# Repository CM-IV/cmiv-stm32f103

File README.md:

## Introduction

[*Project Link*](https://github.com/CM-IV/cmiv-stm32f103-rs)

A few months ago, my embedded systems experience was limited to collecting temperature and accelerometer data on an ESP32-C3 dev board using Rust. Coming from a computer science background, I had written plenty of C++ code and JavaScript in my first jobs out of college, but aside from school studies I didn't know much about the hardware side of things. I noticed the ESP32-C3-DevKit-RUST-1 dev board and decided try it out, but working with pre-built development boards only showed me half the picture.

I wanted to understand the *why* behind the hardware: Why does I²C require pull-up resistors? Why does my carefully written Rust code fail when the PCB layout is flawed? To answer these questions, I embarked on designing my own 2-layer STM32F103 breakout board in KiCAD 9 (on GNU/Linux, of course). The board includes pinouts for SWD, UART, I²C, and GPIO. This journey was a crash course in humility, teaching me that schematic optimism is no match for LCSC’s inventory constraints. Footprint reviews and BOM checks aren’t just best practices—they’re the difference between a functional PCB and hours of frustration with a soldering iron.

## Design

### Why STM32F103?

I chose the STM32F103 microcontroller for its affordability and versatility. It’s part of the ARM Cortex-M3 series, offering a solid balance of performance and peripherals. With its rich feature set, including SPI, I²C, UART, and GPIO it was perfect for my project.

### Power Delivery

The first step in the design process was laying out the power delivery section of the schematic. Proper power delivery is critical for stable operation. I included 100nF and 10µF decoupling capacitors (C1–C8)—one pair for each VDD pin on the IC. These capacitors help filter noise and stabilize the power supply. Additionally, I added a 120Ω ferrite bead (FB1) to filter power on the analog side, ensuring clean power delivery to sensitive components.

Placement is key. In the PCB layout, these capacitors and the ferrite bead are positioned as close as possible to the microcontroller. This minimizes inductance and ensures reliable power delivery, allowing the microcontroller to boot up as expected.

### Reset Circuit (NRST)

The NRST pin is connected to ground through a 100nF capacitor for electromagnetic shielding and to prevent parasitic reset issues. STM32 microcontrollers have an internal pull-up resistor on the NRST pin, so it can be left floating. For my use case, I'm relying on the SWD pinout for flashing and debugging, making the NRST pin less critical. However, I labeled the NRST net in the schematic for easy identification during PCB design.

### Boot Mode Configuration (BOOT0)

The BOOT0 pin is connected to a 10kΩ series resistor and a single-pole double-throw (SPDT) switch. By default, the switch grounds BOOT0, allowing the microcontroller to boot from flash memory and execute its program. When the switch is toggled to 3.3V, BOOT0 is pulled high, enabling the bootloader for firmware flashing. This simple configuration ensures flexibility during development.

### High-Speed External Clock (HSE)

To improve timing accuracy, I opted for a 16MHz crystal oscillator as the HSE clock source. The oscillator is paired with two 10pF load capacitors to ground. Depending on your oscillator’s specifications, you could use capacitors in the 5pF–25pF range for your project. I calculated the load capacitance using the formula:

$$
C_L = \frac{C_1 \times C_2}{C_1 + C_2} + C_{stray}
$$

Here, $C_{stray}$ accounts for stray capacitance, typically around 5pF. For optimal performance, the stm32f103c8 datasheet mentions that capacitors should be placed as close as possible to the crystal to minimize distortion. Later in the PCB layout images you'll see what I mean by this.  I labeled the oscillator nets as HSE_IN and HSE_OUT for easy identification during PCB layout.

### Pinout Design

The pinout includes connections for SWD, UART, I²C, and GPIO. Each pin is labeled clearly in the schematic to simplify PCB layout and firmware development.  I moved the USART pinouts from their original spot near the USB pin to where they are in the image near the BOOT0 pin.  The two pins for the USB differential pair are pinned out to PA11 and PA13, with the SWD pins are at PA13 and PA14.  Proper pinout design by using STM32CubeIDE ensures compatibility with debugging tools and external peripherals, not to mention an easier time with making the schematic with peripheral pin-outs in the first place.

### PCB Layout

The schematic design so far has gotten us to this point, where we route the traces and place the components on the PCB itself.  The power supply and step-down from 5V to 3V3 lives on the right side of the PCB with the necessary capacitors net labeled C12 and C13.  The HSE labeled Y1 has its required capacitors in close proximity, those are labeled C10 and C11.  The rest of the ceramic decoupling capacitors are very close to the IC power pins and allow the device to function as intended.

There are four male headers for the GPIO, SWD, I2C, and UART pins. I'll be able to use jumper wires with a breadboard to do testing and debug the software.  3V3 power is routed to each of these headers with a corresponding ground pin.  The I2C header in particular has 1k5 pull-up resistors so that the logic level is 3V3, it will be at that voltage when no data is being transferred.  I'll probably make a bi-directional level converter to use here later so that it can properly use a 5V powered device.

## Assembly

Once the design was finalized, I exported the Gerber files from KiCAD and sent them to JLCPCB for manufacturing. JLCPCB offers affordable PCB fabrication and assembly services, making it an excellent choice for prototyping. However, I learned the hard way that even with professional assembly services, attention to detail during the design and BOM preparation stages is crucial to avoid headaches later.

### Double-Checking the BOM and Parts

One of the most important lessons I learned during this process was the importance of thoroughly reviewing the Bill of Materials (BOM). While JLCPCB provides an extensive inventory of components, not every part in your schematic may be available. In my case, I overlooked the availability of the USB connector I had specified in the design. As a result, I chose to have JLCPCB assemble the boards without the USB component, leaving me to source and solder it manually on each PCB.

While this was an unexpected challenge, it turned out to be a fun and rewarding experience. Soldering the USB connectors myself gave me a deeper appreciation for the assembly process and the importance of component selection.

#### Tips for Avoiding BOM Issues:
1. **Check Inventory Early:** Before finalizing your schematic, cross-reference your components with JLCPCB's inventory. Their online tool allows you to search for parts and verify availability.
2. **Use Common Components:** Whenever possible, choose widely available parts to reduce the risk of sourcing issues.
3. **Mark Critical Components:** Highlight essential components in your BOM, such as connectors, voltage regulators, and crystals, to ensure they are prioritized during assembly.  Use spreadsheets if needed and plan this out.
4. **Plan for Substitutions:** If your preferred component is unavailable, identify suitable alternatives and update your schematic accordingly.

### Preparing for Manual Soldering

If you find yourself in a situation where certain components need to be soldered manually, here's what I did and the steps I took to make the process smoother:

1. **Source the Missing Components:** I ordered the missing USB component from a reliable supplier, such as Digi-Key or Mouser in the United States. I made EXTRA SURE that the component now matched the footprint on the PCB.
2. **Gather Tools:** I used a fine-tip 40W soldering iron, flux, tweezers, and solder wick for precision work. A magnifying glass also helped quite a bit here.
3. **Practice on a Spare PCB:** If you're new to soldering, practice on a spare PCB or prototyping board to build confidence.
4. **Follow a Workflow:** Start by cleaning the pads with flux, positioning the component using tweezers, and soldering one pin to secure it. Then, solder the remaining pins, ensuring good contact and avoiding cold joints.

In my case, soldering the USB connectors manually was straightforward. The footprint was well-designed, with ample space around the pads for easy access. I found the process enjoyable, and it gave me a sense of accomplishment knowing I had contributed to the assembly process directly.

### Final Assembly Checklist

Before sending your design to JLCPCB, use this checklist to ensure a smooth assembly process:

1. **Review the Schematic:** Double-check all connections, especially power delivery and critical signal paths.
2. **Verify Footprints:** Ensure all components have correct footprints and match the parts in your BOM.
3. **Inspect the PCB Layout:** Check for issues like overlapping traces, misaligned solder masks, or insufficient clearance.
4. **Cross-Reference the BOM:** Confirm that all components are available in JLCPCB's inventory or plan for manual soldering.
5. **Generate Assembly Files:** Export the pick-and-place file and assembly drawings to guide JLCPCB during the manufacturing process.

## Lessons Learned

Designing a custom PCB is as much about planning as it is about execution. Here are some key takeaways:

1. **Inventory Constraints:** Always check component availability before finalizing your schematic.
2. **Documentation Matters:** Clear net labels and pinout diagrams save time during PCB design.
3. **Placement is Critical:** Proper component placement minimizes noise and improves reliability.

## Next Steps

With the basic STM32F103 breakout board complete, I plan to:

1. **Expand Functionality:** Add features like SPI and CAN bus for more advanced projects in a later board revision.
2. **ESD Protection:** Add and place correctly components that mitigate elecrostatic discharge.
3. **Develop Firmware:** Write reusable libraries for peripherals in Rust.

Stay tuned for updates and the first Rust program that I flash to the device!

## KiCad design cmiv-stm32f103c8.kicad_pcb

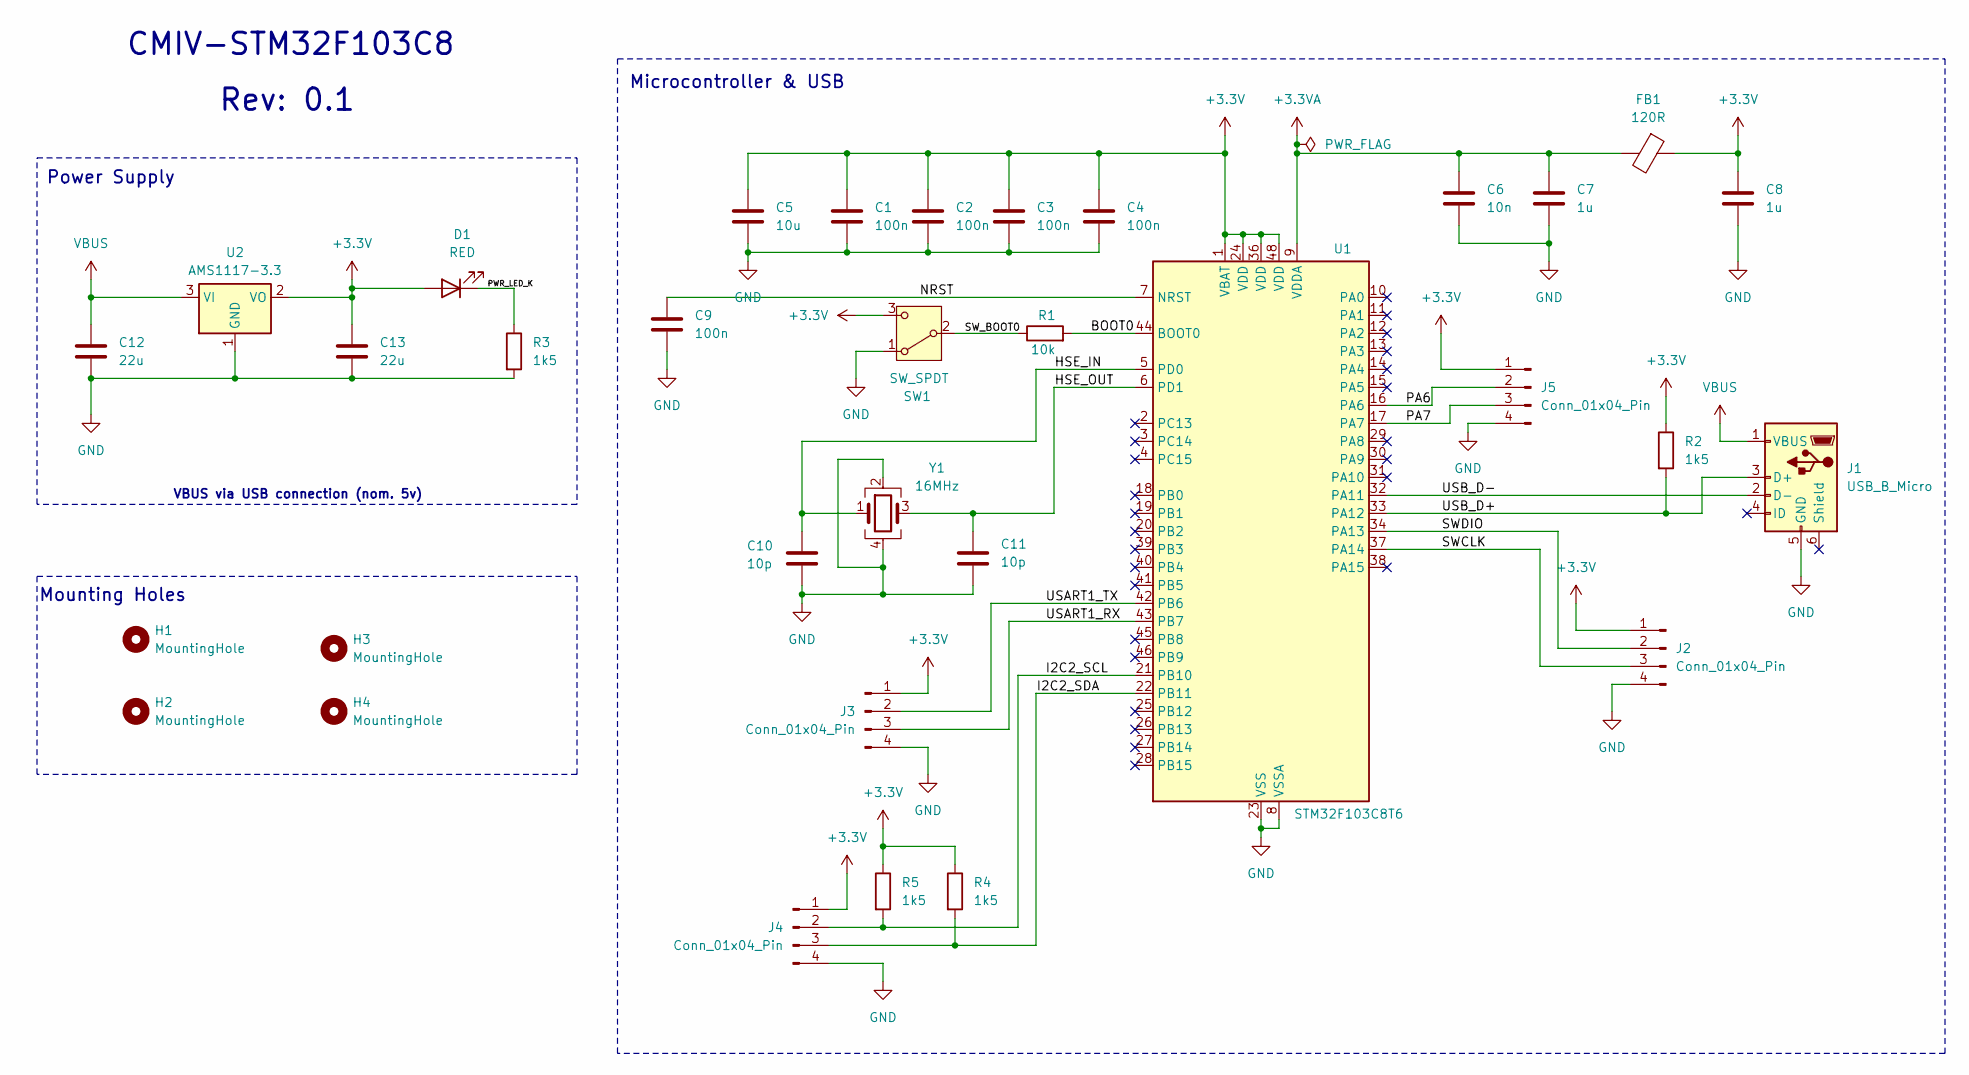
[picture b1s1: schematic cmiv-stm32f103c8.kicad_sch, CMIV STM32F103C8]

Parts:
C1, C2, C3, C4, C9: 100n; C_0402_1005Metric
C5: 10u; C_0603_1608Metric
C6: 10n; C_0402_1005Metric
C7, C8: 1u; C_0402_1005Metric
C10, C11: 10p; C_0402_1005Metric
C12, C13: 22u; C_0805_2012Metric
D1: RED; LED_0603_1608Metric
FB1: 120R; L_0603_1608Metric
H1, H2, H3, H4: MountingHole; MountingHole_2.2mm_M2
J1: USB_B_Micro; USB_Micro-B_XKB_U254-051T-4BH83-F1S
J2, J3, J4, J5: Conn_01x04_Pin; PinHeader_1x04_P2.54mm_Vertical
R1: 10k; R_0402_1005Metric
R2, R3, R4, R5: 1k5; R_0402_1005Metric
SW1: SW_SPDT; SW_SPDT_PCM12
U1: STM32F103C8T6; LQFP-48_7x7mm_P0.5mm
U2: AMS1117-3.3; SOT-223-3_TabPin2
Y1: 16MHz; Crystal_SMD_3225-4Pin_3.2x2.5mm

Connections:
+3.3V: C1.1, C2.1, C3.1, C4.1, C5.1, C8.1, C13.1, D1.2 (A), FB1.1, J2.1, J3.1, J4.1, J5.1, R2.1, R4.1, R5.1, SW1.3 (C), U1.1 (VBAT), U1.24 (VDD), U1.36 (VDD), U1.48 (VDD), U2.2 (VO); also elsewhere on the board
+3.3VA: C6.1, C7.1, FB1.2, U1.9 (VDDA)
/BOOT0: R1.2, U1.44 (BOOT0)
/HSE_IN: C10.1, U1.5 (PD0), Y1.1
/HSE_OUT: C11.1, U1.6 (PD1), Y1.3
/I2C2_SCL: J4.2, R5.2, U1.21 (PB10)
/I2C2_SDA: J4.3, R4.2, U1.22 (PB11)
/NRST: C9.1, U1.7 (NRST)
/PA6: J5.2, U1.16 (PA6)
/PA7: J5.3, U1.17 (PA7)
/PWR_LED_K: D1.1 (K), R3.1
/SWCLK: J2.3, U1.37 (PA14)
/SWDIO: J2.2, U1.34 (PA13)
/SW_BOOT0: R1.1, SW1.2 (B); also elsewhere on the board
/USART1_RX: J3.3, U1.43 (PB7)
/USART1_TX: J3.2, U1.42 (PB6)
/USB_D+: J1.3 (D+), R2.2, U1.33 (PA12); also elsewhere on the board
/USB_D-: J1.2 (D-), U1.32 (PA11); also elsewhere on the board
GND: C1.2, C2.2, C3.2, C4.2, C5.2, C6.2, C7.2, C8.2, C9.2, C10.2, C11.2, C12.2, C13.2, J1.5 (GND), J2.4, J3.4, J4.4, J5.4, R3.2, SW1.1 (A), U1.8 (VSSA), U1.23 (VSS), U1.35 (VSS), U1.47 (VSS), U2.1 (GND), Y1.2, Y1.4; also elsewhere on the board
VBUS: C12.1, J1.1 (VBUS), U2.3 (VI); also elsewhere on the board

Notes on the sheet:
Rev: 0.1
Power Supply
VBUS via USB connection (nom. 5v)
Mounting Holes
CMIV-STM32F103C8
Microcontroller & USB

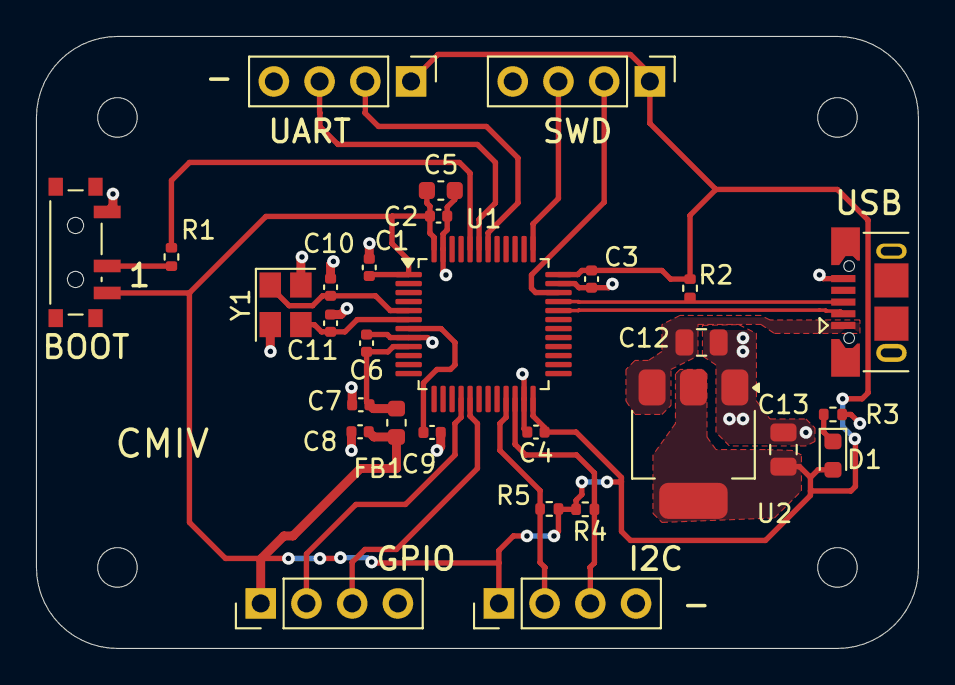
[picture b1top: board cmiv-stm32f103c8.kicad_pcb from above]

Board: 2 copper layers, 49.0 x 34.0 mm, 33 parts (0 on the bottom side), 20 nets.

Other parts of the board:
BOOT: SW_SPDT; SW_SPDT_PCM12
USB: USB_B_Micro; USB_Micro-B_XKB_U254-051T-4BH83-F1S

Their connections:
+3.3V: BOOT.3 (C); also elsewhere on the board
/SW_BOOT0: BOOT.2 (B); also elsewhere on the board
/USB_D+: USB.3 (D+); also elsewhere on the board
/USB_D-: USB.2 (D-); also elsewhere on the board
GND: BOOT.1 (A), USB.5 (GND); also elsewhere on the board
VBUS: USB.1 (VBUS); also elsewhere on the board

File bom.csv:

Designator,Footprint,Quantity,Value,LCSC Part #
BOOT,SW_SPDT_PCM12,1,SW_SPDT,C221841
"C1, C2, C3, C4, C9",402,5,100n,C77020
"C10, C11",402,2,10p,C76946
"C12, C13",805,2,22u,C602037
C5,603,1,10u,C19702
C6,402,1,10n,C15195
"C7, C8",402,2,1u,C14445
FB1,603,1,120R,C14709
"J2, J3, J4, J5",PinHeader_1x04_P2.54mm_Vertical,4,Conn_01x04_Pin,C2691448
ON,603,1,RED,C965799
R1,402,1,10k,C60490
"R2, R3, R4, R5",402,4,1k5,C114759
U1,LQFP-48_7x7mm_P0.5mm,1,STM32F103C8T6,C8734
U2,SOT-223-3_TabPin2,1,AMS1117-3.3,C347222
USB,USB_Micro-B_Wuerth_629105150521,1,USB_B_Micro,C505111
Y1,Crystal_SMD_3225-4Pin_3.2x2.5mm,1,16MHz,C127500
